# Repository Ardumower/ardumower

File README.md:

# Ardumower

## Download
__WARNING__: Do not use the master version (via download button), that is 'code we work on' and it may be unstable - use one release version instead (click on 'releases' link below)!

https://github.com/Ardumower/ardumower/releases

## Reporting a bug / Fehler melden
[Click here!](https://github.com/Ardumower/ardumower/issues/new?title=Error+XYZ+%2F+Fehler+XYZ&body=Please+always+fill-in+below%2FBitte+unbedingt+ausf%C3%BCllen%21%0D%0A%0D%0A--English--%0D%0AYour+battery+voltage+%2812v%2C+24v%29%3A+24v%0D%0AYour+gear+motor+%28Ardumower%2C+other%29%3A+Ardumower+motor%0D%0AYour+Ardumower+software+version+%28pfodApp-%3EInfo%29%3A+890%0D%0AYour+Arduino+%28Mega+or+Due%29%3A+Mega+2560%0D%0AYour+PCB+version+%28printed+on+PCB%29%3A+0.5%0D%0AYour+PCB+mounted+parts+configuration+%28default+or+custom+and+how%29%3A+default%0D%0AOdometry+sensor+%28yes%2Fno%29%3F+yes%0D%0AArdumower+chassis+%28yes%2Fno%29%3F+yes%0D%0AExact+error+description%3A+...+%0D%0A%0D%0A--Deutsch--%0D%0ADeine+Akku-Spannung+%2812v%2C+24v%29%3A+24v%0D%0ADein+Antriebsmotor+%28Ardumower%2C+anderer%29%3A+Ardumower+Motor%0D%0ADeine+Ardumower-Software+Version%3A+%28pfodApp-%3EInfo%29%3A+890%0D%0ADeine+PCB-Version+%28siehe+Aufdruck%29%3A+0.5%0D%0ADein+Arduino+%28Mega+oder+Due%29%3A+Mega+2560%0D%0ADeine+PCB+Bauteilbest%C3%BCckung+%28Standard+oder+abweichend+und+wie%29%3A+Standard%0D%0AOdometrie+sensor+%28ja%2Fnein%29%3F+ja%0D%0AArdumower+Chassis+%28ja%2Fnein%29%3F+ja%0D%0AGenaue+Fehlerbeschreibung%3A+...%0D%0A) 

## Description
Develop an open source robotic lawn mower (HW+SW reference platform)

## Project site
http://www.ardumower.de

## Wiki site
http://wiki.ardumower.de

## This repository contains
* Ardumower robot code (Arduino code)
* Ardumower perimeter sender code (Arduino code)
* Ardumower PCB schematics (PDF, KiCAD)
* Ardumower simulator (requires CodeBlocks - see installation details here:  http://wiki.ardumower.de/index.php?title=Sensor_fusion#SLAM_simulation)
* Ardumower tests (MC33926, DS1307, LM386, HCSR04, GY-80, ESP8266, HB200A, MPU9150, HC-05, PfodApp)

## License
Ardumower (www.ardumower.de)
<br>Copyright (c) 2015-2017 by Uwe Zimprich
<br>Copyright (c) 2014-2015 by Stefan Manteuffel
<br>Copyright (c) 2014 by Walter Crauwels
<br>Copyright (c) 2013-2015 by Sven Gennat
<br>Copyright (c) 2013-2017 by Alexander Grau
<br>Copyright (c) 2014 by Maxime Carpentieri
<br>Copyright (c) 2015-2017 by Juergen Lange    

Private-use only! (you need to ask for a commercial-use)
 
The code/schematics/PCB files are open: you can modify it under the terms of the 
GNU General Public License as published by the Free Software Foundation, 
either version 3 of the License, or (at your option) any later version.

The code/schematics/PCB files are distributed in the hope that it will be useful,
but WITHOUT ANY WARRANTY; without even the implied warranty of
MERCHANTABILITY or FITNESS FOR A PARTICULAR PURPOSE.  See the
GNU General Public License for more details.

You should have received a copy of the GNU General Public License
along with this program.  If not, see <http://www.gnu.org/licenses/>.

Private-use only! (you need to ask for a commercial-use)

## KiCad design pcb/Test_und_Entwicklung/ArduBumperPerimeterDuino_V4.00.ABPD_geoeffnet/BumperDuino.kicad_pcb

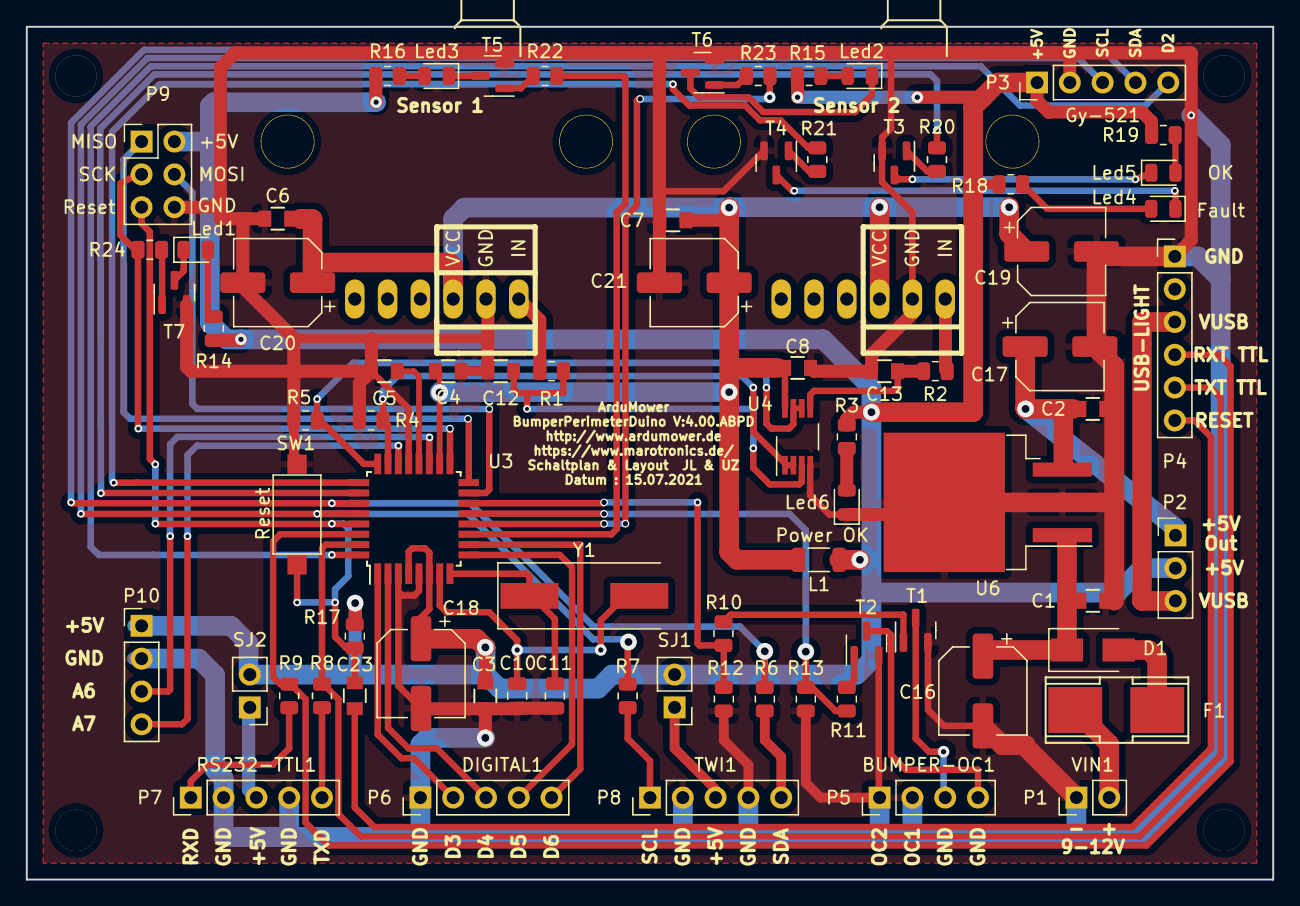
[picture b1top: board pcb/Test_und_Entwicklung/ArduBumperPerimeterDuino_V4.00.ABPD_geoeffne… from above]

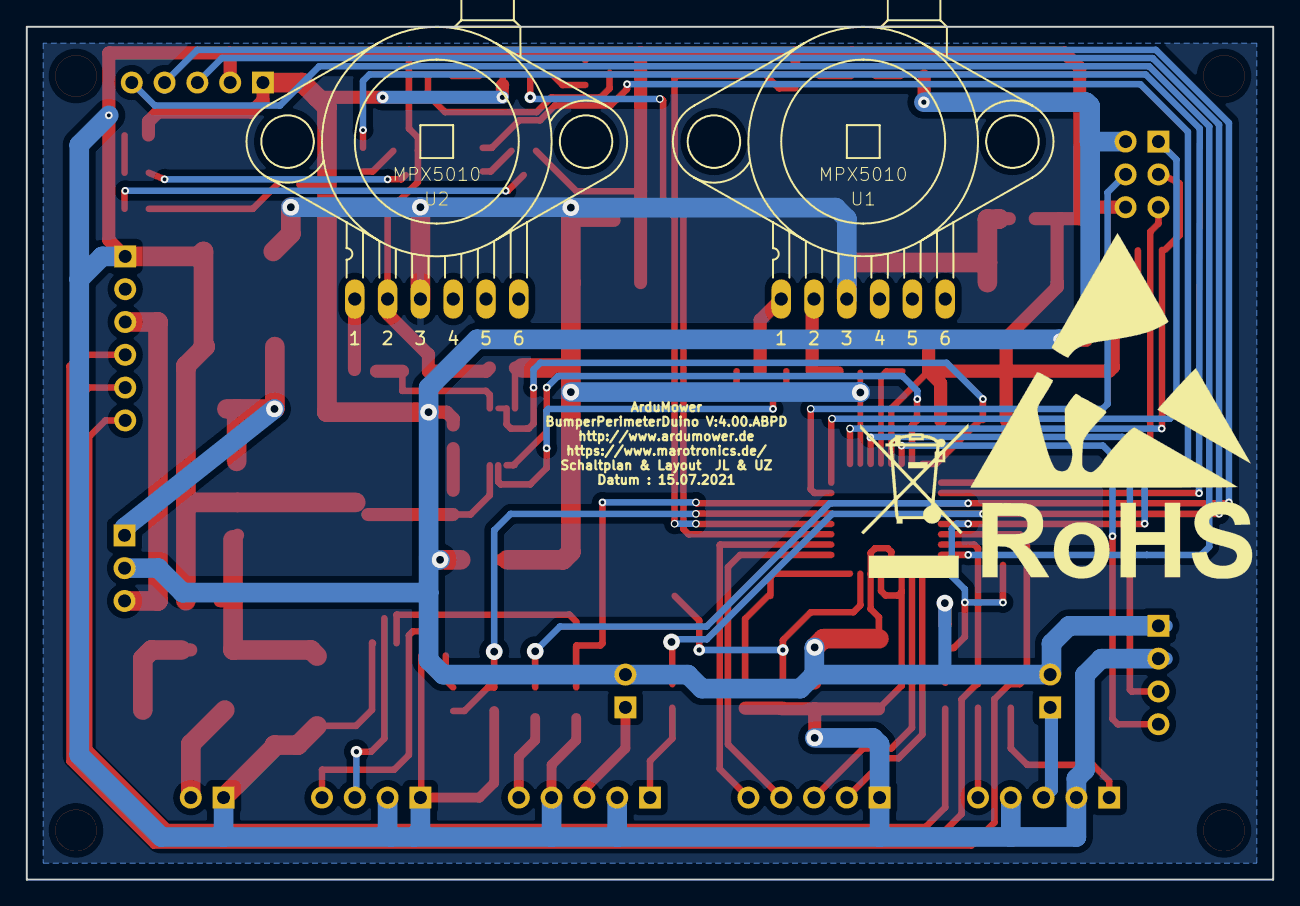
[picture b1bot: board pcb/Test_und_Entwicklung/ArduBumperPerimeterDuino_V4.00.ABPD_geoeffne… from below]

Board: 2 copper layers, 96.5 x 66.0 mm, 85 parts (5 on the bottom side), 65 nets.

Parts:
B1, B2, B3, B4: Bohrloch; Bohrloch_3,2mm
B5: Mülleimer; WEEE-Logo_8.4x12mm_SilkScreen
B6: Rohos; RoHS-Logo_6mm_SilkScreen
B7: ESD-Logo; ESD-Logo_22x20mm_SilkScreen
C1, C2, C3, C4, C5, C6, C7, C8, C23: 100nF; C_0805
C10, C11: 20pF; C_0805_2012Metric
C12, C13: 330nF; C_0805
C16, C18, C19, C20, C21: 10uF; CP_Elec_6.3x5.8
C17: 22uF; CP_Elec_6.3x7.7
D1: S 1G SMD; D_SMA
F1: PTC; Fuse_SMD
L1: 10uH; L_1206_3216Metric
Led1, Led2, Led3, Led4, Led5, Led6: Led; LED_0805_2012Metric
P1: Conn_01x02; PinHeader_1x02_P2.54mm_Vertical
P2: Conn_01x03; PinHeader_1x03_P2.54mm_Vertical
P3, P6, P7, P8: Conn_01x05; PinHeader_1x05_P2.54mm_Vertical
P4: Conn_01x06; PinHeader_1x06_P2.54mm_Vertical
P5, P10: Conn_01x04; PinHeader_1x04_P2.54mm_Vertical
P9: ICSP; PinHeader_2x03_P2.54mm_Vertical
R1, R2: 680; R_0805_2012Metric
R3, R14, R15, R16, R18, R19: 220; R_0805_2012Metric
R4, R5, R12, R13: 10K; R_0805_2012Metric
R6, R7, R8, R9: 100; R_0805_2012Metric
R10, R11, R20, R21, R22, R23, R24: 2,7K; R_0805_2012Metric
R17: 1K; R_0805_2012Metric
SJ1, SJ2: Jumper_NC_Small; PinHeader_1x02_P2.54mm_Vertical
SW1: Reset; SW_SPST_CK_RS282G05A3
T1, T2, T3, T4, T5, T6, T7: BC817; SOT-23
U1, U2: MPX5010
U3: ATmega328-A; TQFP-32_7x7mm_P0.8mm
U4: OPA2340PA; VSSOP-8_3.0x3.0mm_P0.65mm
U6: LM2940CS-5.0; TO-263-3_TabPin4
Y1: Crystal; Crystal_SMD_HC49-SD

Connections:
+5V: C3.2, C18.1, L1.1, P2.2, P3.1, P9.2, P10.1, R3.2, R14.2, R15.2, R16.2, R17.2, R18.2, R19.2, SJ1.2, SJ2.2, U3.4 (VCC), U3.6 (VCC)
A6: P10.3, U3.19 (ADC6)
A7: P10.4, U3.22 (ADC7)
ADC0: R4.2, U3.23 (PC0), U4.1 (OUT_A), U4.2 (-IN_A)
ADC1: R5.2, U3.24 (PC1), U4.6 (-IN_B), U4.7 (OUT_B)
BUMPER-OC1: R11.2, R13.1, U3.13 (PB1)
BUMPER-OC2: R10.2, R12.1, U3.14 (PB2)
D2: P3.5, U3.32 (PD2)
D3: P6.2, U3.1 (PD3)
D4: P6.3, U3.2 (PD4)
D5: P6.4, U3.9 (PD5)
D6: P6.5, U3.10 (PD6)
GND: C1.2, C2.2, C3.1, C4.2, C5.2, C6.2, C7.2, C8.2, C10.2, C11.2, C12.2, C13.2, C16.2, C17.2, C18.2, C19.2, C20.2, C21.2, Led6.1 (K), P1.1, P3.2, P4.1, P5.1, P5.2, P6.1, P7.2, P7.4, P8.2, P8.4, P9.6, P10.2, R4.1, R5.1, R12.2, R13.2, SW1.2, T1.2 (E), T2.2 (E), T3.2 (E), T4.2 (E), T5.2 (E), T6.2 (E), T7.2 (E), U1.2 (GND), U2.2 (GND), U3.3 (GND), U3.5 (GND), U3.21 (GND), U4.4 (V-), U6.2 (GND_2), U6.4 (GND)
LED-COL1: R22.2, U3.11 (PD7)
LED-COL2: R23.2, U3.12 (PB0)
LED-CRASH: R21.2, U3.25 (PC2)
LED-INIT-OK: R20.2, U3.26 (PC3)
MISO: P9.1, U3.16 (PB4)
MOSI: P9.4, U3.15 (PB3)
unnamed: C1.1, C16.1, D1.1 (K), U6.1 (IN)
unnamed: C5.1, U3.20 (AREF)
unnamed: C10.1, U3.7 (XTAL1/PB6), Y1.2
unnamed: C11.1, U3.8 (XTAL2/PB7), Y1.1
unnamed: C12.1, R1.2, U4.3 (+IN_A)
unnamed: C13.1, R2.2, U4.5 (+IN_B)
unnamed: C2.1, C17.1, P2.1, U6.3 (OUT)
unnamed: C23.1, P4.6
unnamed: D1.2 (A), F1.2
unnamed: F1.1, P1.2
unnamed: Led1.1 (K), T7.3 (C)
unnamed: Led1.2 (A), R14.1
unnamed: Led2.1 (K), T6.3 (C)
unnamed: Led2.2 (A), R15.1
unnamed: Led3.1 (K), T5.3 (C)
unnamed: Led3.2 (A), R16.1
unnamed: Led4.1 (K), T4.3 (C)
unnamed: Led4.2 (A), R18.1
unnamed: Led5.1 (K), T3.3 (C)
unnamed: Led5.2 (A), R19.1
unnamed: Led6.2 (A), R3.1
unnamed: P5.3, T1.3 (C)
unnamed: P5.4, T2.3 (C)
unnamed: P7.1, R9.2
unnamed: P7.3, SJ2.1
unnamed: P7.5, R8.2
unnamed: P8.1, R7.2
unnamed: P8.3, SJ1.1
unnamed: P8.5, R6.2
unnamed: R1.1, U1.1 (VOUT)
unnamed: R2.1, U2.1 (VOUT)
unnamed: R10.1, T1.1 (B)
unnamed: R11.1, T2.1 (B)
unnamed: R20.1, T3.1 (B)
unnamed: R21.1, T4.1 (B)
unnamed: R22.1, T5.1 (B)
unnamed: R23.1, T6.1 (B)
unnamed: R24.1, T7.1 (B)
RXD_TTL: P4.4, R9.1, U3.30 (PD0)
Reset: C23.2, P9.5, R17.1, SW1.1, U3.29 (~RESET/PC6)
SCK: P9.3, R24.2, U3.17 (PB5)
SCL: P3.3, R7.1, U3.28 (PC5)
SDA: P3.4, R6.1, U3.27 (PC4)
TXD_TTL: P4.5, R8.1, U3.31 (PD1)
VCC: C4.1, C6.1, C7.1, C8.1, C19.1, C20.1, C21.1, L1.2, U1.3 (VCC), U2.3 (VCC), U3.18 (AVCC), U4.8 (V+)
VUSB: P2.3, P4.3

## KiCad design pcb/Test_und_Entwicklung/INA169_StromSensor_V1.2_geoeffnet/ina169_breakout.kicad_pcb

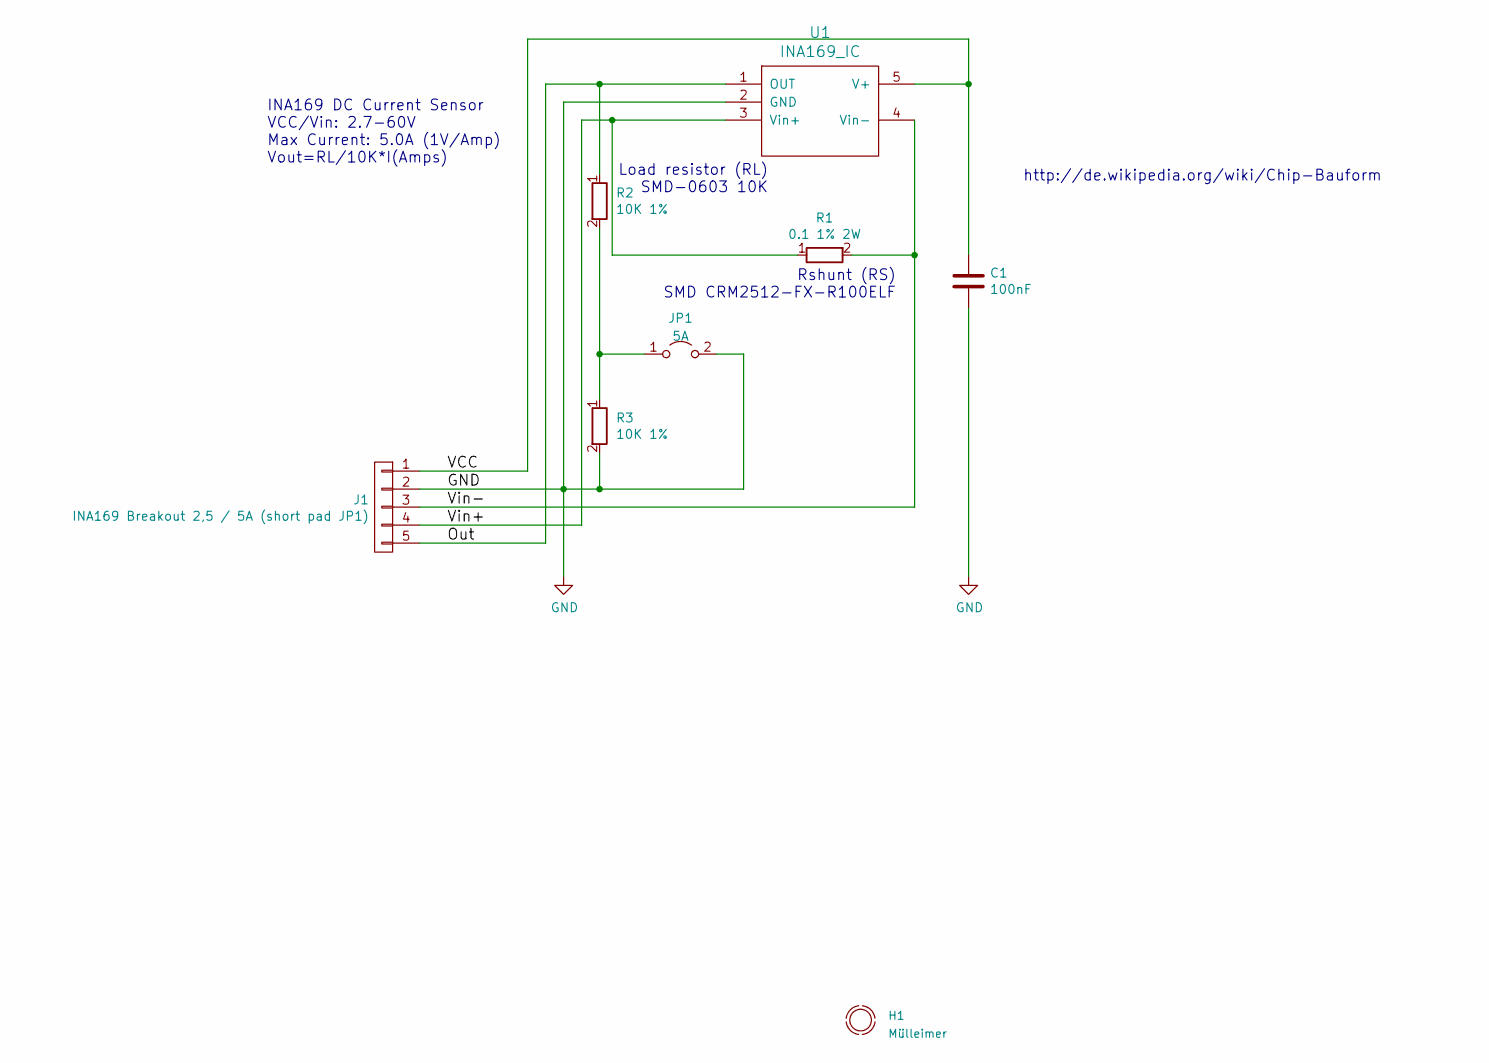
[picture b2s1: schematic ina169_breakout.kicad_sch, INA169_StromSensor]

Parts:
C1: 100nF; C_1206; JLCPCB Basic / Extern Basic
H1: Mülleimer; WEEE-Logo_4.2x6mm_SilkScreen; JLCPCB Basic / Extern Value
J1: INA169 Breakout 2,5 / 5A (short pad JP1); ina169_breakout_footprint_mit_unterem_Lötpad; JLCPCB Basic / Extern Value
JP1: 5A; SolderJumper-2_P1.3mm_Open_Pad1.0x1.5mm; JLCPCB Basic / Extern Value
R1: 0.1 1% 2W; R_2512; JLCPCB Basic / Extern Extern
R2, R3: 10K 1%; R_0603; JLCPCB Basic / Extern Basic
U1: INA169_IC; SOT-23-5; JLCPCB Basic / Extern Extern

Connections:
/Out: J1.5, R2.1, U1.1 (OUT)
/VCC: C1.1, J1.1, U1.5 (V+)
/Vin+: J1.4, R1.1, U1.3 (Vin+)
/Vin-: J1.3, R1.2, U1.4 (Vin-)
GND: C1.2, J1.2, JP1.2 (B), R3.2, U1.2 (GND)
unnamed: JP1.1 (A), R2.2, R3.1

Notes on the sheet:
INA169 DC Current Sensor VCC/Vin: 2.7-60V Max Current: 5.0A (1V/Amp) Vout=RL/10K*I(Amps)
Load resistor (RL) SMD-0603 10K
Rshunt (RS) SMD CRM2512-FX-R100ELF
http://de.wikipedia.org/wiki/Chip-Bauform

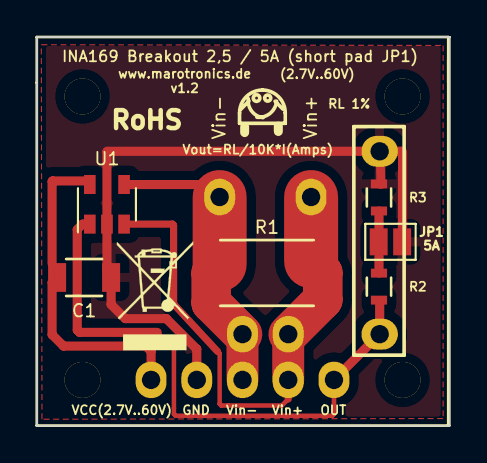
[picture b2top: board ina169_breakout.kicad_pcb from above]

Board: 2 copper layers, 22.9 x 21.6 mm, 8 parts (0 on the bottom side), 6 nets.

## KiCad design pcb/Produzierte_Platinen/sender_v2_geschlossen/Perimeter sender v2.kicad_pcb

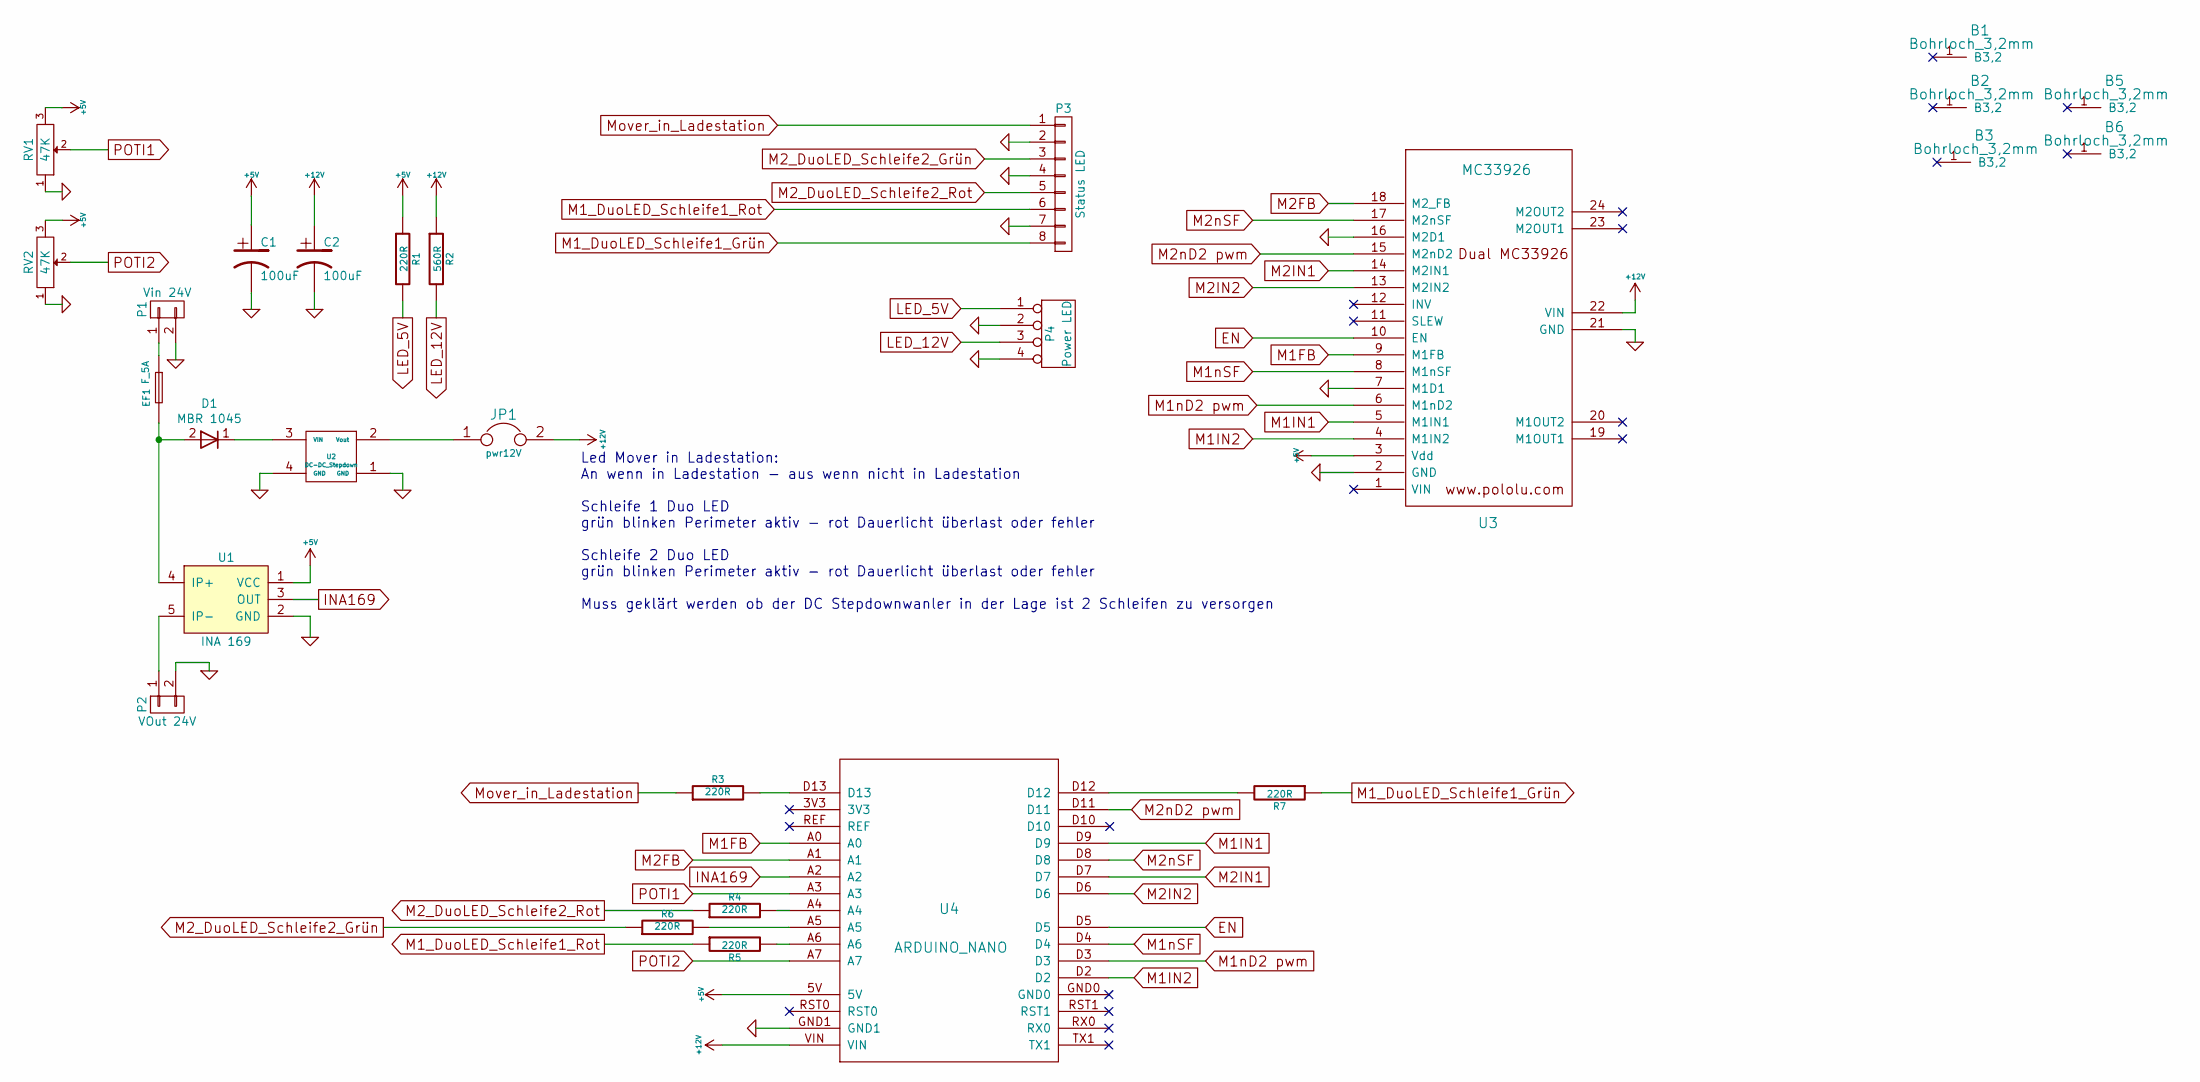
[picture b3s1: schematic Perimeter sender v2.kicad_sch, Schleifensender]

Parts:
B1, B2, B3, B5, B6: Bohrloch_3,2mm
C1, C2: 100uF; Elko_vert_11.2x6.3mm_RM2.5_RM5.0
D1: MBR 1045; MBR1045_Horizontal
EF1: F_5A; Fuseholder_Reichelt_PL112000
JP1: pwr12V; Pin_Header_Straight_1x02
P1: Vin 24V; Anschlussklemme_2P_RM5,08
P2: VOut 24V; Anschlussklemme_2P_RM5,08
P3: Status LED; PinHeader_1x08_P2.54mm_Vertical
P4: Power LED; PinHeader_1x04_P2.54mm_Vertical
R1, R3, R4, R5, R6, R7: 220R; Resistor_Horizontal_RM10mm
R2: 560R; Resistor_Horizontal_RM10mm
RV1, RV2: 47K; Potentiometer_VishaySpectrol-Econtrim-Type36T_3D-angepasst_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
U1: INA 169; INA169
U2: DC-DC_Stepdown; DC_DC_DSN2596_mit_Bohrloch
U3: MC33926; MC_33926_31polig_mit_Bohrloch_neue_Masse
U4: ARDUINO_NANO; arduino_nano

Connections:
+5V: C1.1, R1.1, RV1.3, RV2.3, U1.1 (VCC), U3.3 (Vdd), U4.5V
+12V: C2.1, JP1.2, R2.1, U3.22 (VIN), U4.VIN
EN: U3.10 (EN), U4.D5
GND: C1.2, C2.2, P1.2, P2.2, P3.2, P3.4, P3.7, P4.2, P4.4, RV1.1, RV2.1, U1.2 (GND), U2.1 (GND), U2.4 (GND), U3.2 (GND), U3.7 (M1D1), U3.16 (M2D1), U3.21 (GND), U4.GND1
INA169: U1.3 (OUT), U4.A2
LED_5V: P4.1, R1.2
LED_12V: P4.3, R2.2
M1FB: U3.9 (M1FB), U4.A0
M1IN1: U3.5 (M1IN1), U4.D9
M1IN2: U3.4 (M1IN2), U4.D2
M1_DuoLED_Schleife1_Grün: P3.8, R7.1
M1_DuoLED_Schleife1_Rot: P3.6, R5.1
M1nD2 pwm: U3.6 (M1nD2), U4.D3
M1nSF: U3.8 (M1nSF), U4.D4
M2FB: U3.18 (M2_FB), U4.A1
M2IN1: U3.14 (M2IN1), U4.D7
M2IN2: U3.13 (M2IN2), U4.D6
M2_DuoLED_Schleife2_Grün: P3.3, R6.1
M2_DuoLED_Schleife2_Rot: P3.5, R4.1
M2nD2 pwm: U3.15 (M2nD2), U4.D11
M2nSF: U3.17 (M2nSF), U4.D8
Mover_in_Ladestation: P3.1, R3.1
unnamed: D1.1 (K), U2.3 (VIN)
unnamed: D1.2 (A), EF1.1, U1.4 (IP+)
unnamed: EF1.2, P1.1
unnamed: JP1.1, U2.2 (Vout)
unnamed: P2.1, U1.5 (IP-)
unnamed: R3.2, U4.D13
unnamed: R4.2, U4.A4
unnamed: R5.2, U4.A6
unnamed: R6.2, U4.A5
unnamed: R7.2, U4.D12
POTI1: RV1.2, U4.A3
POTI2: RV2.2, U4.A7

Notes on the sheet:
Led Mover in Ladestation: An wenn in Ladestation - aus wenn nicht in Ladestation Schleife 1 Duo LED grün blinken Perimeter aktiv - rot Dauerlicht überlast oder fehler Schleife 2 Duo LED grün blinken Perimeter aktiv - rot Dauerlicht überlast oder fehler Muss geklärt werden ob der DC Stepdownwanler i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

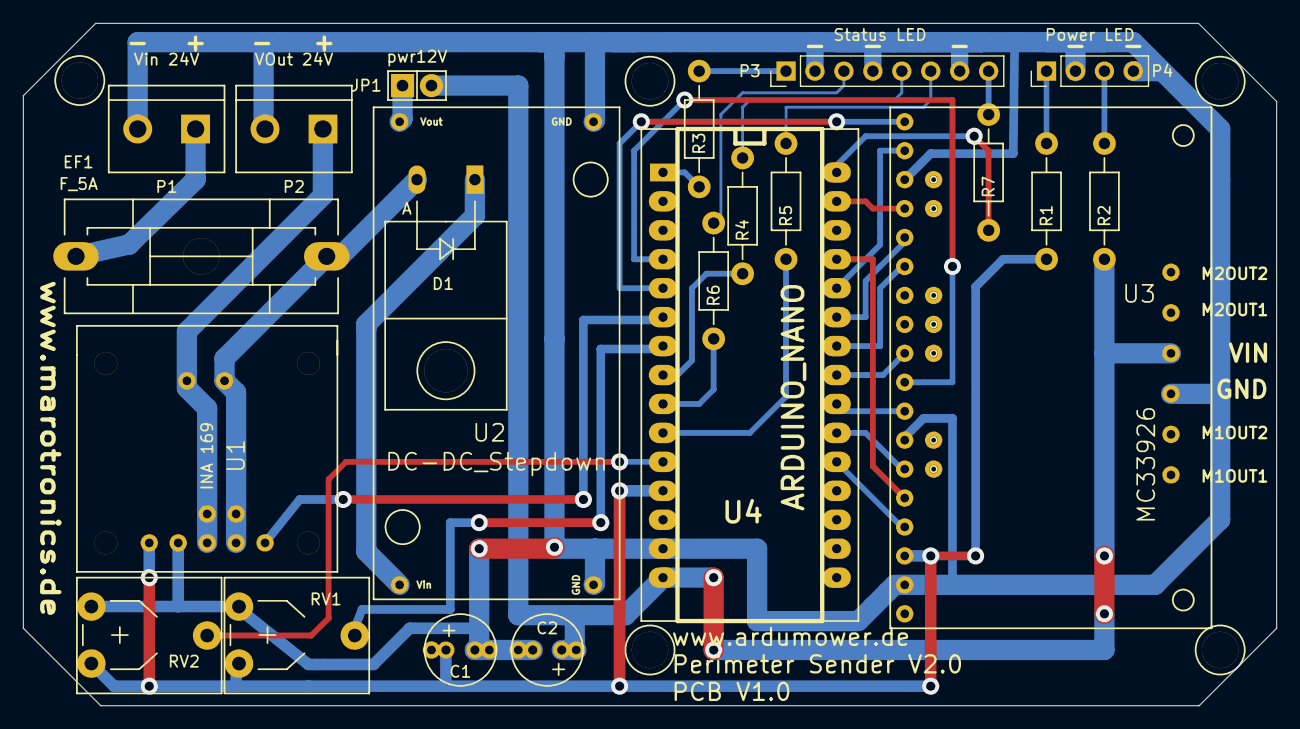
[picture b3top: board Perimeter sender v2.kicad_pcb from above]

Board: 2 copper layers, 110.0 x 59.9 mm, 27 parts (0 on the bottom side), 34 nets.

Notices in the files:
ardumower1/config.h:
Copyright (c) 2013-2014 by Alexander Grau
Copyright (c) 2013-2014 by Sven Gennat
This program is free software: you can redistribute it and/or modify
